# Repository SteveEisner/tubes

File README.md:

# tubes
These portable LED light poles make pretty lights for a dance party - and better yet:

They're **portable**! Convenient tripod bases keep them standing at attention, and a 10Ah USB battery (like the one you charge your phone with) will power them for about 8 hours.

They're **versatile**! You can deploy them in a [wide open space at Burning Man](https://youtu.be/UtXL0ScNUoE), in a [private event space](https://youtu.be/B6OBde7zRN4), or right next to each other [in your living room](https://youtu.be/UmiRBCOAMBg).  (Click into these links for videos of them in action.)

They're **coordinated**! If you put them next to each other, they sync using near-field radio. And they'll even daisy-chain, meaning the furthest ones can be really far apart as long as there are some in the middle to relay the signal.

They're **sturdy**! I built 20 of them and deployed them at parties in all kinds of weather, from hot & dusty windstorms to torrential rain. They've been tossed in a truck, carried around as totems, knocked or blown over, and almost all of 'em are still working.  Just don't let people use them like light sabers (lesson learned.)

They're also **in progress** with lots of things that could be improved.  But for now:

* they play patterns from an expanding set of "genetically-driven" combinations
* they stay in sync or deliberately drift from each other in pleasing ways
* they operate internally at a certain BPM - allowing them to sync to music

### How do they work?

Each light tube is running custom software on a Teensy LC (Arduino-compatible) microcontroller. The software is running a generative light program that has a simple "DNA" specifying its pattern, color, effects overlay, offset, and so on.

The patterns run on a clock that's synced to a specific BPM and counts out the 4/4 rhythm of most dance music, so they morph and change on individual beats, measures, and phrases. After several beat phrases pass, a pole's DNA is mutated a little, which can cause it to change color, or adopt a new pattern, etc.

An on-board NRF radio lets a light pole broadcast its DNA and clock timer; when others hear the signal, they can choose to follow along by updating their own pattern DNA to match it. The method of coordination is pretty simple right now: each pole has an 8-bit ID, and lower-ID poles obey higher-ID poles.

If they're all close enough, they'll soon start doing the same thing as a group and keeping their clock timers in sync. In case they're not close enough, poles also re-broadcast all the signals they receive and obey. This lets them pass along a signal through the group until all of them have found it.

Some randomness and chaos is intentional. Radio isn't 100% reliable, so they sometimes fall out of contact and then re-connect. And in some cases, the poles will deliberately offset their own clock a bit so that they are clearly doing the same thing but not exactly at the same time. Each tube is actually running several copies of the software and smoothly "cross-fading" between them, to avoid any jarring transitions.

### Want your own?

They're not for sale, but check out the build instructions in [this directory](assembly), complete with a parts list & assembly instructions. I'd love it if you build your own!

### Credits

The form factor was inspired by [Mark Lottor's Hexatron](http://www.3waylabs.com/projects/hex/). The color schemes were inspired by [the work of Christopher Schardt](https://americanart.si.edu/exhibitions/burning-man/online/christopher-schardt) and many were found on [cpt-city](http://soliton.vm.bytemark.co.uk/pub/cpt-city/).  The code was written using [FastLED](http://fastled.io/) and most patterns are evolved versions of FastLED examples.  It's based on [Chuck Sommerville's led-swarm](https://github.com/chucks13/LED-swarm), and still follows its [theory](https://github.com/chucks13/LED-swarm/blob/master/theory.txt) for radio connection. I used [Paul Stoffregen's WS2812Serial](https://github.com/PaulStoffregen/WS2812Serial) for smooth animation, and of course [his Teensy CPU](https://www.pjrc.com/teensy/teensyLC.html) made the whole thing possible. Standing on the shoulders of these giants let me create these in about a month, in time to debut at Burning Man 2019 and appear at many parties since!

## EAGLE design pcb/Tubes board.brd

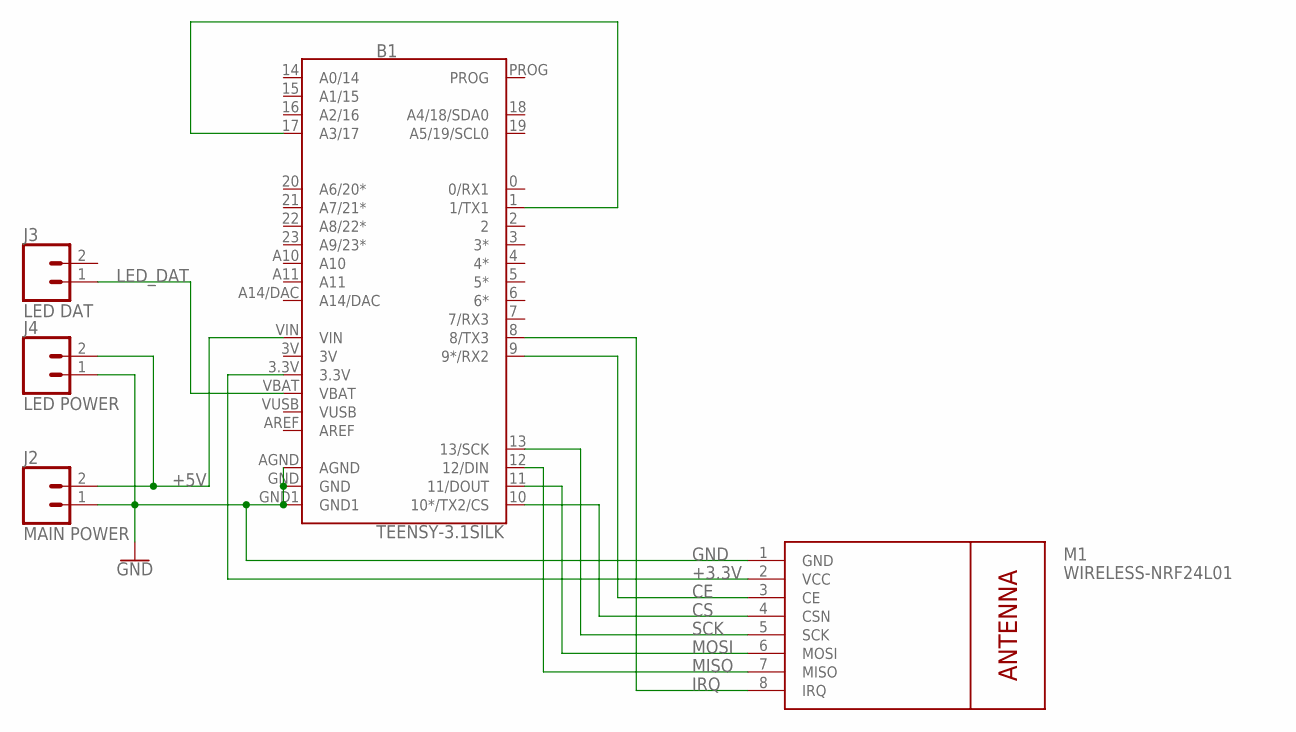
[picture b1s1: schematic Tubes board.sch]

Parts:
B1: TEENSY-3.1SILK; TEENSY-3.1
J2: MAIN POWER; SCREWTERMINAL-5MM-2
J3: LED DAT; SCREWTERMINAL-5MM-2
J4: LED POWER; SCREWTERMINAL-5MM-2
M1: WIRELESS-NRF24L01

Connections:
3V: B1.3V
+3.3V: B1.3.3V, M1.2 (VCC)
+5V: B1.VIN, J2.2, J4.2
CE: B1.9 (9*/RX2), M1.3 (CE)
CS: B1.10 (10*/TX2/CS), M1.4 (CSN)
DAT: B1.1 (1/TX1), B1.17 (A3/17)
GND: B1.AGND, B1.GND, B1.GND1, J2.1, J4.1, M1.1 (GND)
IRQ: B1.8 (8/TX3), M1.8 (IRQ)
LED_DAT: B1.VBAT, J3.1
MISO: B1.12 (12/DIN), M1.7 (MISO)
MOSI: B1.11 (11/DOUT), M1.6 (MOSI)
SCK: B1.13 (13/SCK), M1.5 (SCK)
VUSB: B1.VUSB

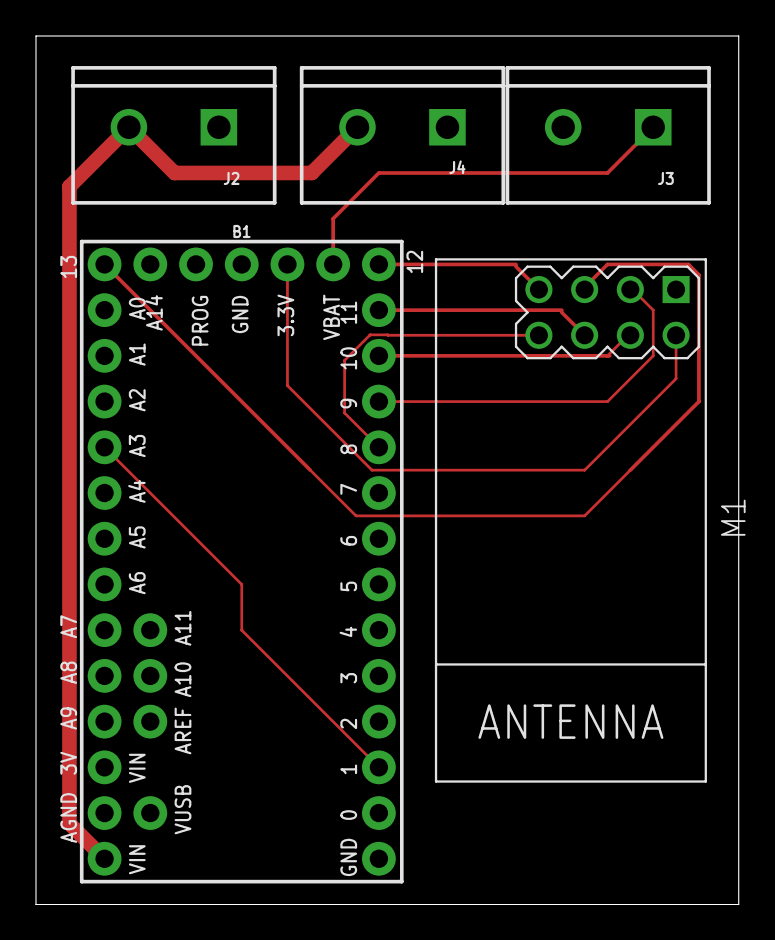
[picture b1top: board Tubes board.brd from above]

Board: 2 copper layers, 39.0 x 48.2 mm, 5 parts (0 on the bottom side), 11 nets.

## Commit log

2019-08-08 Initial checkin
2019-08-09 Use WS2812Serial for nonblocking; BPMs sync much better now
2019-08-10 New buttons; memory optimizations
2019-08-10 Reverse controller/radio dependencies
2019-08-12 Rework master/slave code & prepare for message relaying
2019-08-12 Relayed commands; serial monitoring
2019-08-12 BPM debugging
2019-08-12 New flash animation; better control over changes
2019-08-13 Reorganize timers and create beat fracs
2019-08-13 Broadcast option changes
2019-08-14 Revert timer changes and just make patterns change only on a phrase
2019-08-14 Fix crash due to overallocation of particles; move button logic into controller
2019-08-15 New palettes
2019-08-16 missing file; spammy error
2019-08-16 fix palettes
2019-08-16 Rework animations to add more particle effects
2019-08-16 Mega effects update
2019-08-16 Mega patterns update
2019-08-16 Tweaks
2019-08-17 Gimpy keyboard support
2019-08-19 Fixes
2019-08-20 More cleanup and debugging of patterns
2019-08-21 Fixing
2019-08-22 Fixes for the Burn
2019-08-22 More pre-burn work
2019-08-22 More fixes
2019-08-23 pre-burn final checkin
2019-08-24 move master controls to master.h and fix joystick
2019-08-24 Brightness control
2019-08-25 Manual BPM
2019-08-29 Palette control
2019-08-29 Button 1 effects
2019-09-14 Check in the master controller; add PCB data
2019-09-14 Add missing wire
2019-09-14 Wire IRQ
2019-09-15 parts list
2019-09-15 Update README.md
    Reformatted markdown
2019-09-28 Visual Studio Code installation
2019-11-07 Convert to PlatformIO
2021-09-20 Fix warnings
2021-09-20 Add assembly instructions
2021-09-20 New home page
2021-09-21 Update home page and assembly instructions
2021-09-24 Fix typos and bad link
2022-05-02 update to latest ustd library
2022-05-02 Allow compilation on Teensy 3.X, 4.X, LC
2022-05-02 Redefine static struct initializers to support all architectures
2022-05-02 ustd declares freeMemory, so I don't have to
2022-05-02 pragma once is much nicer
2022-05-02 got it compiling for ESP32 (by turning off radio)
2022-05-03 Re-enable NRF radio for ESP32

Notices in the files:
parts and their libraries:
SparkFun-Boards: Licensing: Creative Commons ShareAlike 4.0 International - https://creativecommons.org/licenses/by-sa/4.0
diy-modules: Released under the Creative Commons Attribution 4.0 International License: http://creativecommons.org/licenses/by/4.0
